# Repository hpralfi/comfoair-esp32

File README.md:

# comfoair-esp32

**Zehnder ComfoAir, StorkAir WHR oder Wernig G90 in Home Assistant einbinden — lokal, ohne Cloud und ohne MQTT.**

[English](README.en.md) · [Projektseite](https://hpralfi.github.io/comfoair-esp32/)

Eine kleine ESP32-Platine für die Buchse **„RS232 PC“** von Lüftungsgeräten mit der Zehnder-Steuerplatine CA350. Sie läuft mit [ESPHome](https://esphome.io) und erscheint in Home Assistant mit über 40 Entitäten: Temperaturen, Lüftungsstufe, Ventilatorleistung und Drehzahl, Bypass, Filterzustand, Frostschutz, Betriebsstunden.

Entstanden ist sie als Ersatz für einen Gira HomeServer mit Moxa-Seriell-Gateway an einer Wernig G90-380. Dort läuft sie seit Oktober 2026.

## Funktionen

- **Native Home-Assistant-Anbindung** über die ESPHome-API — kein MQTT-Broker, keine Cloud
- **Alle Werte des Geräts**: vier Temperaturen, Stufe, Leistung und Drehzahl der Ventilatoren, Bypass, Filter, Frostschutz, Vorheizung, Betriebsstunden je Stufe
- **Steuern**: Lüftungsstufe 0–3, Komforttemperatur, Stufenwerte in Prozent, Stoßlüften-Taster auf der Platine
- **Schalter für das Bedienteil**: CC-Ease / CC-Luxe parallel weiter nutzen oder dunkel schalten, sodass nur Home Assistant bedient (siehe [RS232-Modus](#rs232-modus-und-das-bedienteil))
- **Eigene Weboberfläche** im Browser (mit Anmeldung): Stufenwahl, Wärmetauscher-Schaubild mit allen vier Temperaturen, Ventilatoren, Filterwarnung, Einstellungen, Live-Log, Firmware-Update per Datei — auch ohne Home Assistant, am Handy wie am PC
- **Updates über WLAN** nach dem ersten Flashen
- **USB-C** für Versorgung und Programmierung (CH340K an Bord, automatischer Wechsel in den Bootloader)
- **Zweiter RS232-Kanal** an einer Schraubklemme, vorgesehen für einen späteren Proxy-Betrieb des Bedienteils
- Status-LED (WS2812B) und ein frei belegbarer Taster

## In Home Assistant

Beispiel-Dashboard: Stufenknöpfe, Schalter für das Bedienteil, Ventilatoren, Bypass, Filter, Betriebsstunden und Temperaturverlauf über 24 Stunden.

## Weboberfläche

Unter `http://<adresse-der-platine>/`, eingebettet in die Firmware ([`firmware/webui/comfoair-ui.js`](firmware/webui/comfoair-ui.js)), braucht kein Internet. Wer die Standardansicht von ESPHome bevorzugt, entfernt in der Konfiguration die Zeilen `js_url` und `js_include`.

## Hardware

| | |
|---|---|
| Größe | 70 × 55 mm, 2 Lagen, 1,6 mm |
| Prozessor | ESP32-WROOM-32E (WLAN, Leiterplattenantenne) |
| Pegelwandler | MAX3232 (2 Kanäle) |
| USB | USB-C, CH340K, ESD-Schutz USBLC6 |
| Versorgung | 5 V über USB-C, Regler AP2112K 3,3 V, unter 1 W |
| Anschluss Gerät | **DB9-Stecker**, DTE-Belegung: Pin 2 RX, Pin 3 TX, Pin 5 GND |
| Zweiter Anschluss | 3-polige Schraubklemme (RS232-Kanal 2) |
| Lötbrücken | JP1/JP2 kreuzen RX/TX am DB9 bei Bedarf |

Der DB9 ist belegt wie bei einer Moxa NPort 5110: Hängt am Gerät schon ein Seriell-Gateway oder PC-Kabel, dieses abstecken und die Platine mit demselben Kabel anschließen. An der Wernig G90-380 war kein Kreuzen nötig.

Schaltplan: [`hardware/schematic.pdf`](hardware/schematic.pdf) · KiCad-Projekt: [`hardware/kicad/`](hardware/kicad/) · Fertigungsdaten: [`hardware/production/`](hardware/production/)

## Kompatible Geräte

Das ComfoAir-Seriellprotokoll sprechen viele Geräte und ihre Handelsmarken-Varianten. Die meisten Kompatibilitätsangaben im Netz sind aus derselben Protokollbeschreibung abgeschrieben — deshalb trennt diese Liste **nachgewiesene** von nur **gelisteten** Geräten.

| Gerät | Marke | Status | Hinweis |
|---|---|---|---|
| G90-380 (CS / Luxe) | Wernig | ✅ **mit dieser Platine nachgewiesen** | meldet „CA350 luxe“, Firmware 3.20 |
| G90-160 | Wernig | ✅ nachgewiesen (andere Projekte) | openHAB-Binding |
| ComfoAir 350 | Zehnder | ✅ nachgewiesen (andere Projekte) | Referenzgerät des Protokolls |
| ComfoAir 160 | Zehnder | ✅ nachgewiesen (andere Projekte) | esphome-comfoair |
| ComfoD 450 | Zehnder | ✅ nachgewiesen (andere Projekte) | |
| G90-200 CS | Wernig | 🟡 wahrscheinlich | „RS232 PC“ im Schaltplan |
| ComfoAir 200 / 500 / 550 | Zehnder | 🟡 wahrscheinlich | gelistet, kein Testbericht |
| ComfoD 300 / 350 / 550 | Zehnder | 🟡 wahrscheinlich | gelistet |
| WHR 920 / 930 / 950 / 960 | J.E. StorkAir | 🟡 wahrscheinlich | gelistet |
| Santos 370 DC | Paul | 🟡 wahrscheinlich | gelistet |
| G90-300 | Wernig | ❔ ungeprüft | Schnittstelle nicht bestätigt |
| ComfoAir Q350 / Q450 / Q600, Wernig Q350 / Q600 | Zehnder / Wernig | ❌ nicht kompatibel | CAN / ComfoNet |
| ComfoAir E300 / E350 / E400 | Zehnder | ❌ nicht kompatibel | Modbus RTU (RS485) |
| Novus 300 | Paul | ❌ nicht kompatibel | RS485 |
| Vitovent 300-W | Viessmann | ❌ nicht kompatibel | OpenTherm / Modbus |

**Ein 🟡-Gerät getestet?** Bitte ein Issue anlegen — es wandert dann zu ✅.

### So prüfst du dein Gerät

1. **Typenschild**: eines der Modelle oben. Ein „Q“ oder „E“ im Modellnamen heißt: passt nicht.
2. **Bedienteil**: CC-Ease (Drehrad mit Display), CC-Luxe oder die alte ComfoSense sind gute Zeichen. ComfoConnect, ComfoSense C oder ein Touch-Display deuten auf die Q-Plattform.
3. **Steuerplatine**: CA350 / CA550 mit einem Anschluss **„RS232“** oder **„RS232 PC“**. Bei manchen Geräten ist das keine DB9-Buchse, sondern RJ45 oder Schraubklemmen (RX/TX/GND) — dann braucht es ein Adapterkabel.
4. Auf der Konnektorplatine der Wernig G90-380 CS gibt es zusätzlich **RS485**-Klemmen („Entalpy“, „Hybalans“). Die sind für Zubehör, **nicht** der PC-Anschluss.

## Platine bekommen

### Fertige Platine

Bestückte und geprüfte Platinen: DB9 und Schraubklemme gelötet, Lötbrücken gesetzt, Firmware aufgespielt.

**Fertige Platinen sind in Vorbereitung.** Melde dich unverbindlich — mit Gerätemodell und Land, dann sage ich Bescheid, sobald es losgeht:

📧 **[office@gfrerrer.at](mailto:office@gfrerrer.at?subject=comfoair-esp32%20-%20Interesse)**

### Selbst bauen

1. Bei [JLCPCB](https://jlcpcb.com) mit Bestückung (PCBA) bestellen: [`gerber.zip`](hardware/production/gerber.zip), [`jlcpcb-bom.csv`](hardware/production/jlcpcb-bom.csv) und [`jlcpcb-cpl.csv`](hardware/production/jlcpcb-cpl.csv) hochladen. Die Bestückungsdatei enthält bereits die Dreh- und Lagekorrekturen, die JLCPCB braucht. Die LCSC-Nummern beim Bestellen auf Lagerbestand prüfen.
2. Von Hand löten: **J2** (DB9-Stecker, gewinkelt, mit Befestigungsbohrungen) und **J3** (3-polige Schraubklemme, 5,08 mm). Auch die beiden Befestigungslaschen des DB9 verlöten — sie tragen die Steckkraft. Sie hängen an der Massefläche: breite Meißelspitze, etwa 380 °C.
3. **Lötbrücken JP1 und JP2 auf Pad 1–2 schließen.** Sie sind ab Werk offen — ohne sie ist der DB9 nicht mit dem MAX3232 verbunden und das Gerät bleibt stumm. (Pad 2–3 kreuzt RX/TX, falls das Kabel es braucht.)
4. Firmware aufspielen (unten).

## Firmware

Die Platine nutzt einen Fork von [wichers/esphome-comfoair](https://github.com/wichers/esphome-comfoair) mit zwei Ergänzungen: RS232-Modus setzen (Kommando `0x9B`) und den vom Gerät gemeldeten Modus auswerten (`0x9C`).

1. [`firmware/comfoair-esp32.yaml`](firmware/comfoair-esp32.yaml), den Ordner [`firmware/webui/`](firmware/webui/) und [`firmware/secrets.yaml.example`](firmware/secrets.yaml.example) (als `secrets.yaml`) in den ESPHome-Ordner kopieren und ausfüllen.
2. Erstes Flashen über USB-C, z. B. mit dem ESPHome-Dashboard oder `esphome run comfoair-esp32.yaml`. Die Platine wechselt selbst in den Bootloader.
3. Danach laufen Updates über WLAN.
4. Home Assistant findet das Gerät; den API-Schlüssel eingeben, wenn danach gefragt wird.
5. Webinterface: `http://<adresse-der-platine>/`, Anmeldung mit `web_username` / `web_password` aus `secrets.yaml`. Dort lassen sich auch neue Firmware-Dateien (`.bin`) hochladen.

## RS232-Modus und das Bedienteil

Das Gerät kennt mehrere RS232-Modi. Gemessen an einer CA350 mit Firmware 3.20:

| Modus | Bedeutung | Ergebnis |
|---|---|---|
| 1 „nur PC“ | | **wird quittiert, aber ignoriert** |
| 3 „PC Master“ | | angenommen — **Bedienteil wird dunkel** |
| 0 „Ende“ (aus 3) | zurück auf 2 „nur CC-Ease“ | Bedienteil aktiv, **Home Assistant liest und schaltet trotzdem** |

Der Schalter **„Wall panel“** in Home Assistant wählt zwischen beiden: aus = Modus 3 (Bedienteil dunkel), an = Modus 2 (beide parallel). Nach einem Stromausfall startet das Gerät in Modus 2; die Platine prüft den gemeldeten Modus jede Minute und stellt die Einstellung wieder her.

## Einbau

- Die Platine hängt **nur an der Kleinspannungs-Schnittstelle RS232**. Den Netzspannungsteil des Geräts nicht öffnen.
- Versorgung über ein beliebiges USB-C-Netzteil (5 V, 0,5 A reichen).
- Das Antennenende der Platine frei von Metall halten, dann ist der WLAN-Empfang gut.
- Auf der RS232-Leitung darf nur **ein Master** sprechen: anderes Gateway oder PC vorher abstecken.

## Lizenz

- Hardware (`hardware/`): [CERN-OHL-S-2.0](LICENSE-CERN-OHL-S-2.0)
- Firmware-Konfiguration und Dokumentation: [GPL-3.0](LICENSE-GPL-3.0), wie die zugrunde liegende ESPHome-Komponente

## Haftungsausschluss

Ein unabhängiges Hobbyprojekt ohne Verbindung zu Zehnder Group, J.E. StorkAir, Wernig oder Paul. Marken- und Modellnamen dienen nur zur Angabe der Kompatibilität. Nutzung auf eigene Gefahr.

## Dank

- [wichers/esphome-comfoair](https://github.com/wichers/esphome-comfoair) — die ESPHome-Komponente
- Die ComfoAir-Protokollbeschreibung der Community sowie die Projekte FHEM, openHAB und hacomfoairmqtt

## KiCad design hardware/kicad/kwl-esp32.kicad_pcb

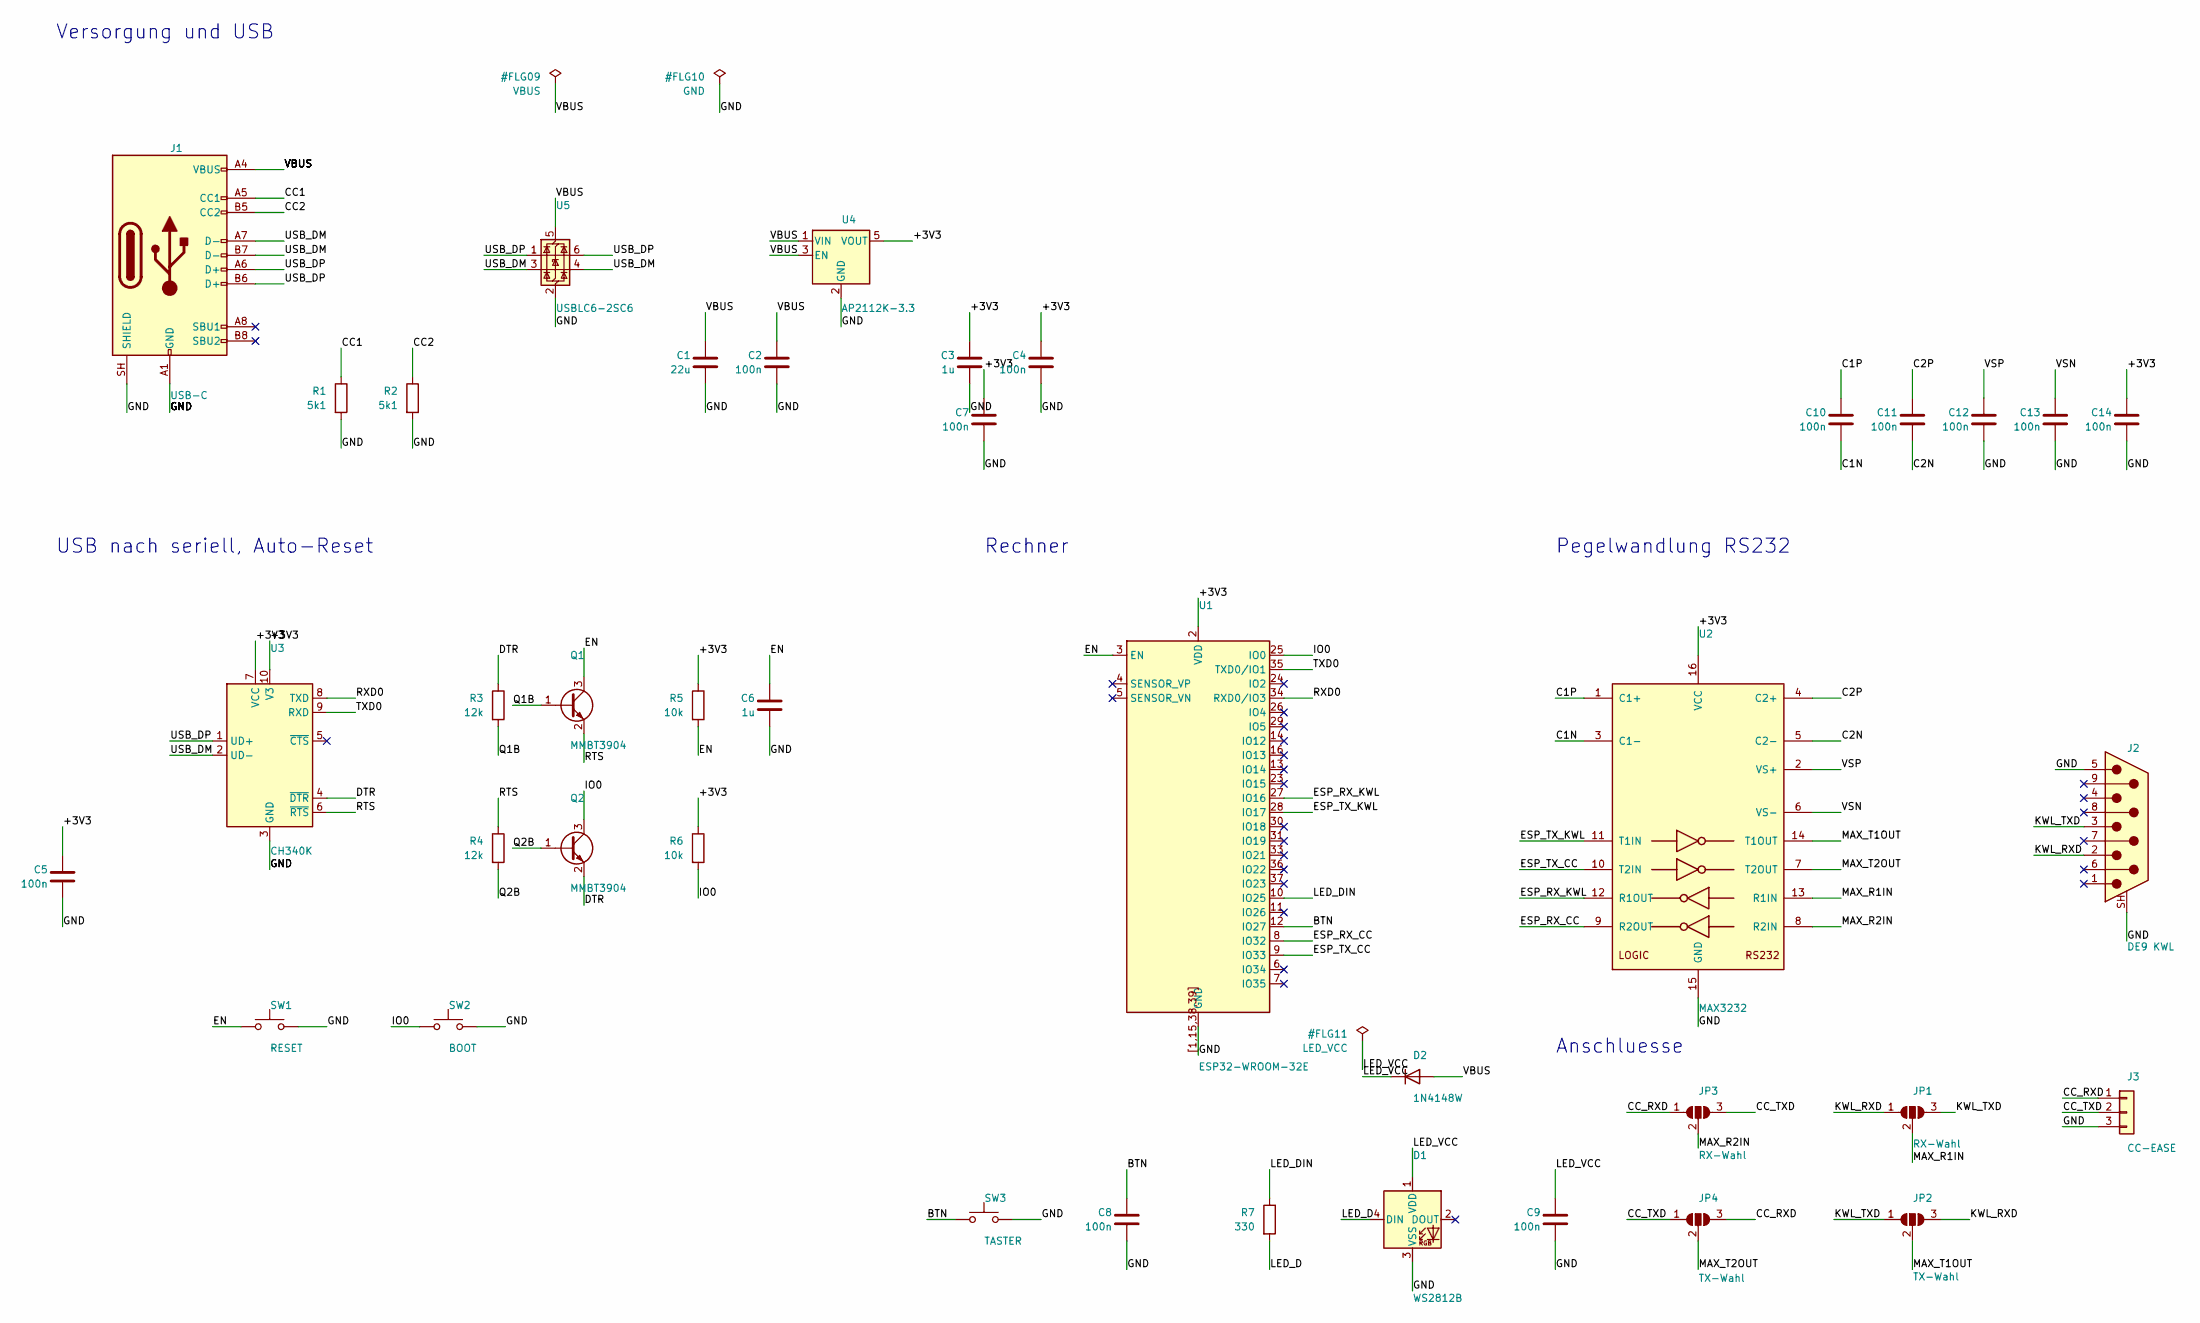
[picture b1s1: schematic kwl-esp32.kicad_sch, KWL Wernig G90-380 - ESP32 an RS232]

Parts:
C1: 22u; C_0805_2012Metric
C2, C4, C5, C7, C8, C9, C10, C11, C12, C13, C14: 100n; C_0603_1608Metric
C3, C6: 1u; C_0603_1608Metric
D1: WS2812B; LED_WS2812B_PLCC4_5.0x5.0mm_P3.2mm
D2: 1N4148W; D_SOD-123
J1: USB-C; USB_C_Receptacle_HRO_TYPE-C-31-M-12
J2: DE9 KWL; DSUB-9_Pins_Horizontal_P2.77x2.84mm_EdgePinOffset4.94mm_Hou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
J3: CC-EASE; TerminalBlock_MaiXu_MX126-5.0-03P_1x03_P5.00mm
JP1, JP3: RX-Wahl; SolderJumper-3_P1.3mm_Open_Pad1.0x1.5mm
JP2, JP4: TX-Wahl; SolderJumper-3_P1.3mm_Open_Pad1.0x1.5mm
Q1, Q2: MMBT3904; SOT-23
R1, R2: 5k1; R_0603_1608Metric
R3, R4: 12k; R_0603_1608Metric
R5, R6: 10k; R_0603_1608Metric
R7: 330; R_0603_1608Metric
SW1: RESET; SW_Push_1P1T_NO_CK_KMR2
SW2: BOOT; SW_Push_1P1T_NO_CK_KMR2
SW3: TASTER; SW_Push_1P1T_NO_CK_KMR2
U1: ESP32-WROOM-32E
U2: MAX3232; SOIC-16_3.9x9.9mm_P1.27mm
U3: CH340K; SSOP-10-1EP_3.9x4.9mm_P1mm_EP2.1x3.3mm
U4: AP2112K-3.3; SOT-23-5
U5: USBLC6-2SC6; SOT-23-6

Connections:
+3V3: C3.1, C4.1, C5.1, C7.1, C14.1, R5.1, R6.1, U1.2 (VDD), U2.16 (VCC), U3.7 (VCC), U3.10 (V3), U4.5 (VOUT)
BTN: C8.1, SW3.1, U1.12 (IO27)
C1N: C10.2, U2.3 (C1-)
C1P: C10.1, U2.1 (C1+)
C2N: C11.2, U2.5 (C2-)
C2P: C11.1, U2.4 (C2+)
CC1: J1.A5 (CC1), R1.1
CC2: J1.B5 (CC2), R2.1
CC_RXD: J3.1, JP3.1 (A), JP4.3 (B)
CC_TXD: J3.2, JP3.3 (B), JP4.1 (A)
DTR: Q2.2 (E), R3.1, U3.4 (~DTR)
EN: C6.1, Q1.3 (C), R5.2, SW1.1, U1.3 (EN)
ESP_RX_CC: U1.8 (IO32), U2.9 (R2OUT)
ESP_RX_KWL: U1.27 (IO16), U2.12 (R1OUT)
ESP_TX_CC: U1.9 (IO33), U2.10 (T2IN)
ESP_TX_KWL: U1.28 (IO17), U2.11 (T1IN)
GND: C1.2, C2.2, C3.2, C4.2, C5.2, C6.2, C7.2, C8.2, C9.2, C12.2, C13.2, C14.2, D1.3 (VSS), J1.A1 (GND), J1.A12 (GND), J1.B1 (GND), J1.B12 (GND), J1.SH (SHIELD), J2.5, J2.SH (PAD), J3.3, R1.2, R2.2, SW1.2, SW2.2, SW3.2, U1.1, U1.15, U1.38, U1.39, U1.[1,15,38,39] (GND), U2.15 (GND), U3.3 (GND), U3.11 (GND), U4.2 (GND), U5.2 (GND)
IO0: Q2.3 (C), R6.2, SW2.1, U1.25 (IO0)
KWL_RXD: J2.2, JP1.1 (A), JP2.3 (B)
KWL_TXD: J2.3, JP1.3 (B), JP2.1 (A)
LED_D: D1.4 (DIN), R7.2
LED_DIN: R7.1, U1.10 (IO25)
LED_VCC: C9.1, D1.1 (VDD), D2.1 (K)
MAX_R1IN: JP1.2 (C), U2.13 (R1IN)
MAX_R2IN: JP3.2 (C), U2.8 (R2IN)
MAX_T1OUT: JP2.2 (C), U2.14 (T1OUT)
MAX_T2OUT: JP4.2 (C), U2.7 (T2OUT)
Q1B: Q1.1 (B), R3.2
Q2B: Q2.1 (B), R4.2
RTS: Q1.2 (E), R4.1, U3.6 (~RTS)
RXD0: U1.34 (RXD0/IO3), U3.8 (TXD)
TXD0: U1.35 (TXD0/IO1), U3.9 (RXD)
USB_DM: J1.A7 (D-), J1.B7 (D-), U3.2 (UD-), U5.3 (I/O2), U5.4 (I/O2)
USB_DP: J1.A6 (D+), J1.B6 (D+), U3.1 (UD+), U5.1 (I/O1), U5.6 (I/O1)
VBUS: C1.1, C2.1, D2.2 (A), J1.A4 (VBUS), J1.A9 (VBUS), J1.B4 (VBUS), J1.B9 (VBUS), U4.1 (VIN), U4.3 (EN), U5.5 (VBUS)
VSN: C13.1, U2.6 (VS-)
VSP: C12.1, U2.2 (VS+)

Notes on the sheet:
Rechner
Pegelwandlung RS232
USB nach seriell, Auto-Reset
Anschluesse
Versorgung und USB

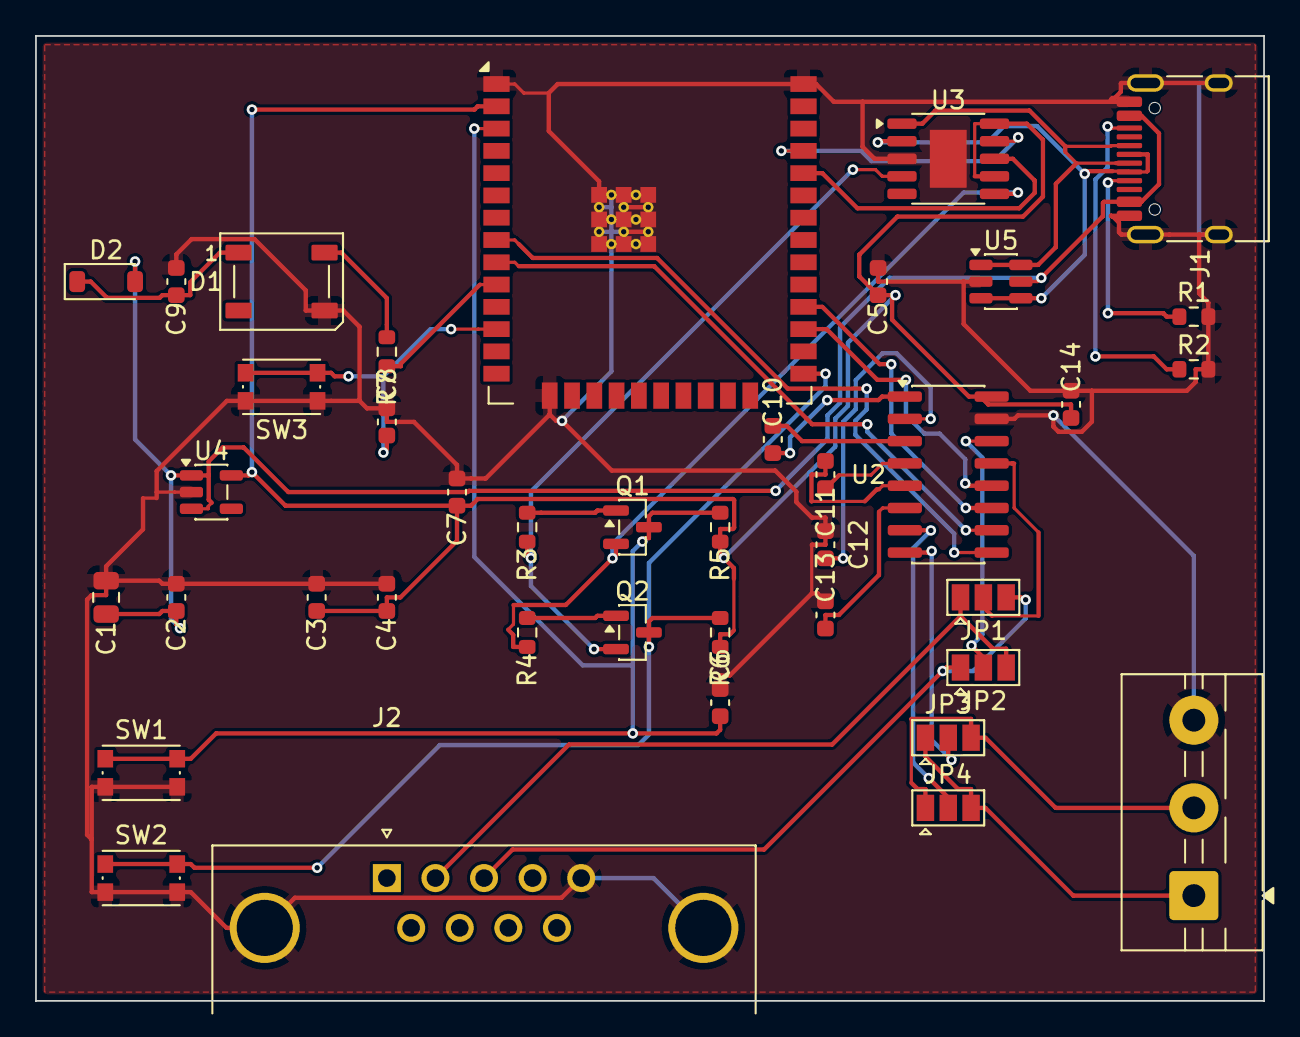
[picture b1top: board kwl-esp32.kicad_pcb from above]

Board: 2 copper layers, 70.0 x 55.0 mm, 40 parts (0 on the bottom side), 37 nets.
